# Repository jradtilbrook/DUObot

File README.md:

# DUObot Project Repository

This repository contains the files related to my two-wheeled balancing robot, aptly named DUObot.

In the extremely rare circumstance that someone actually uses this repository and/or finds a bug, please let me know by opening an issue. I would also welcome any other feedback or contributions.

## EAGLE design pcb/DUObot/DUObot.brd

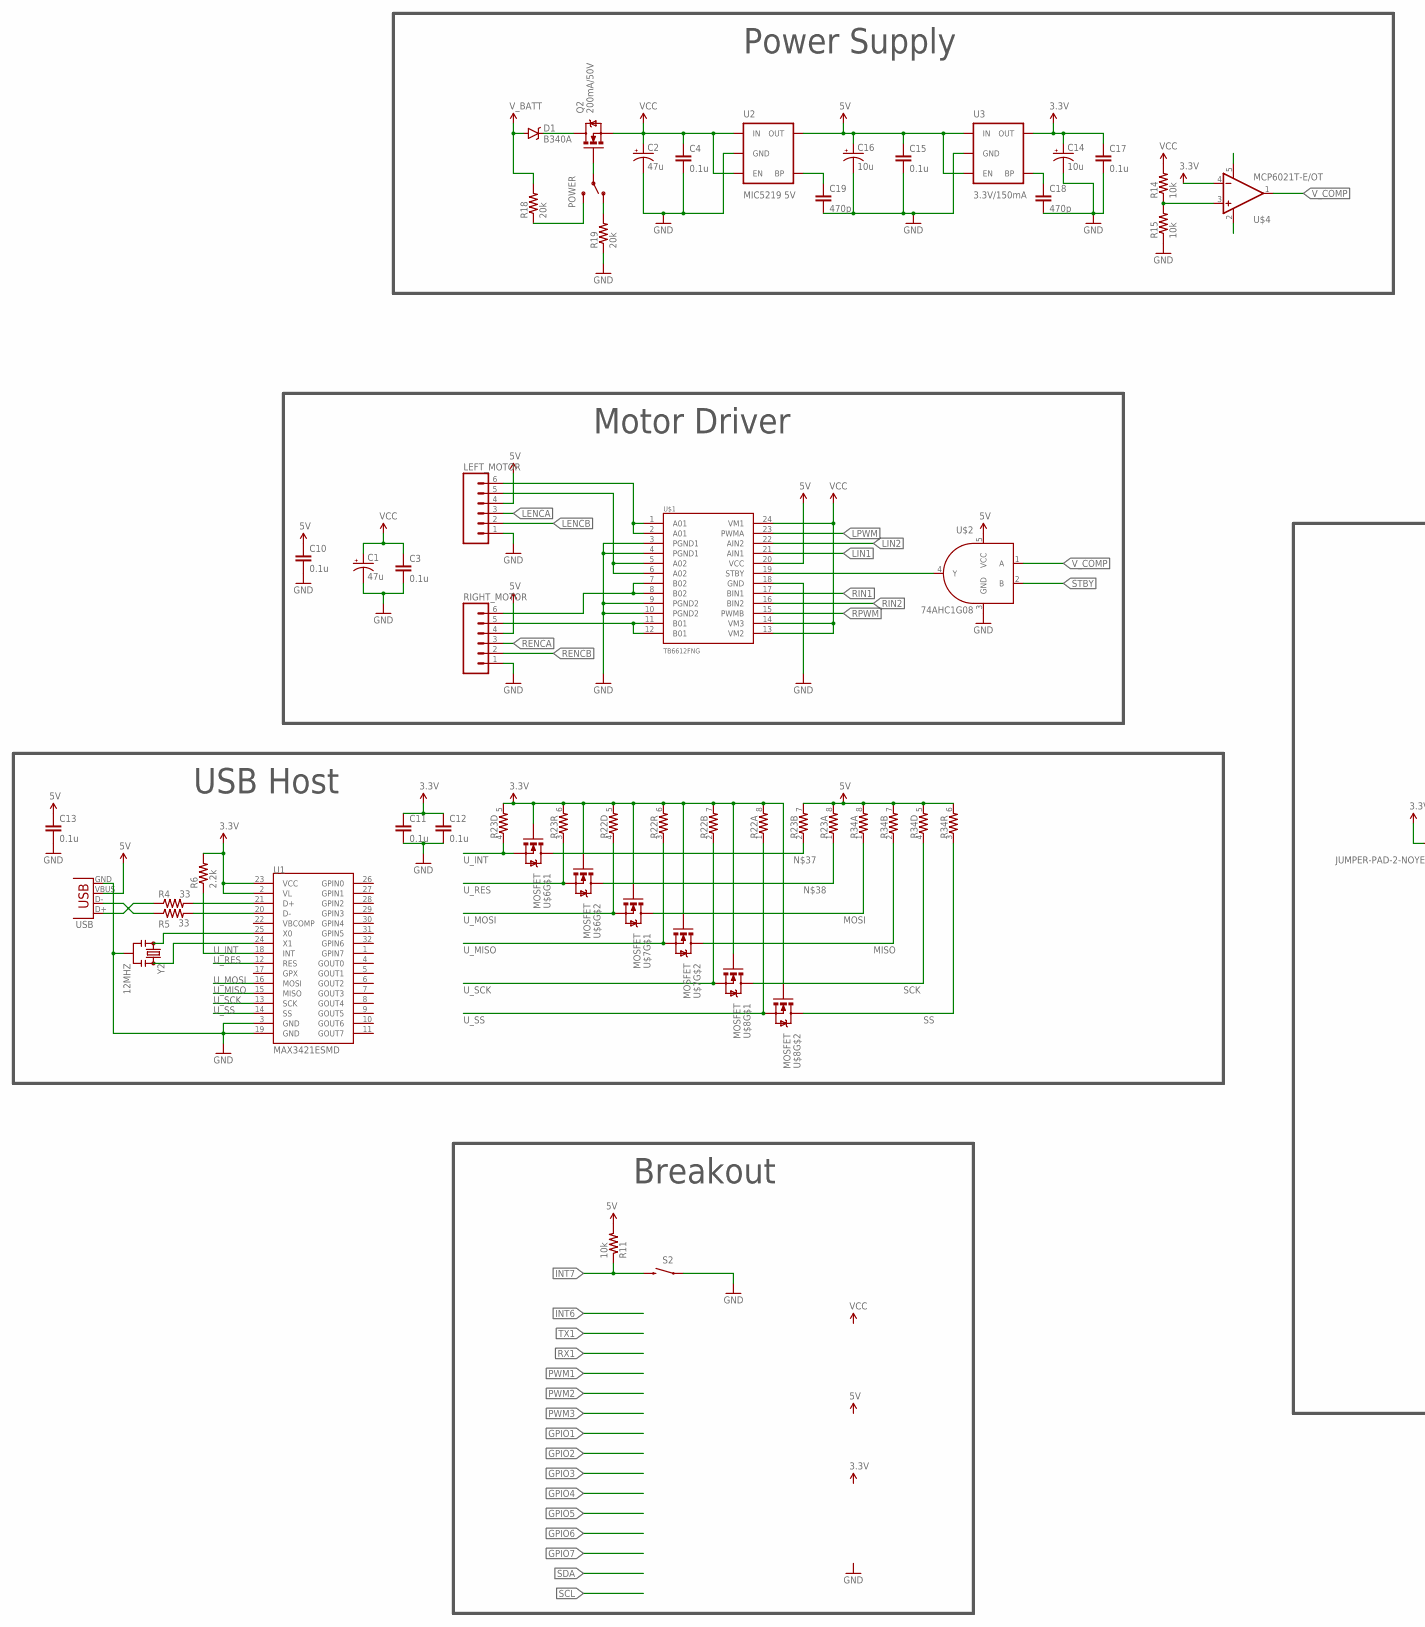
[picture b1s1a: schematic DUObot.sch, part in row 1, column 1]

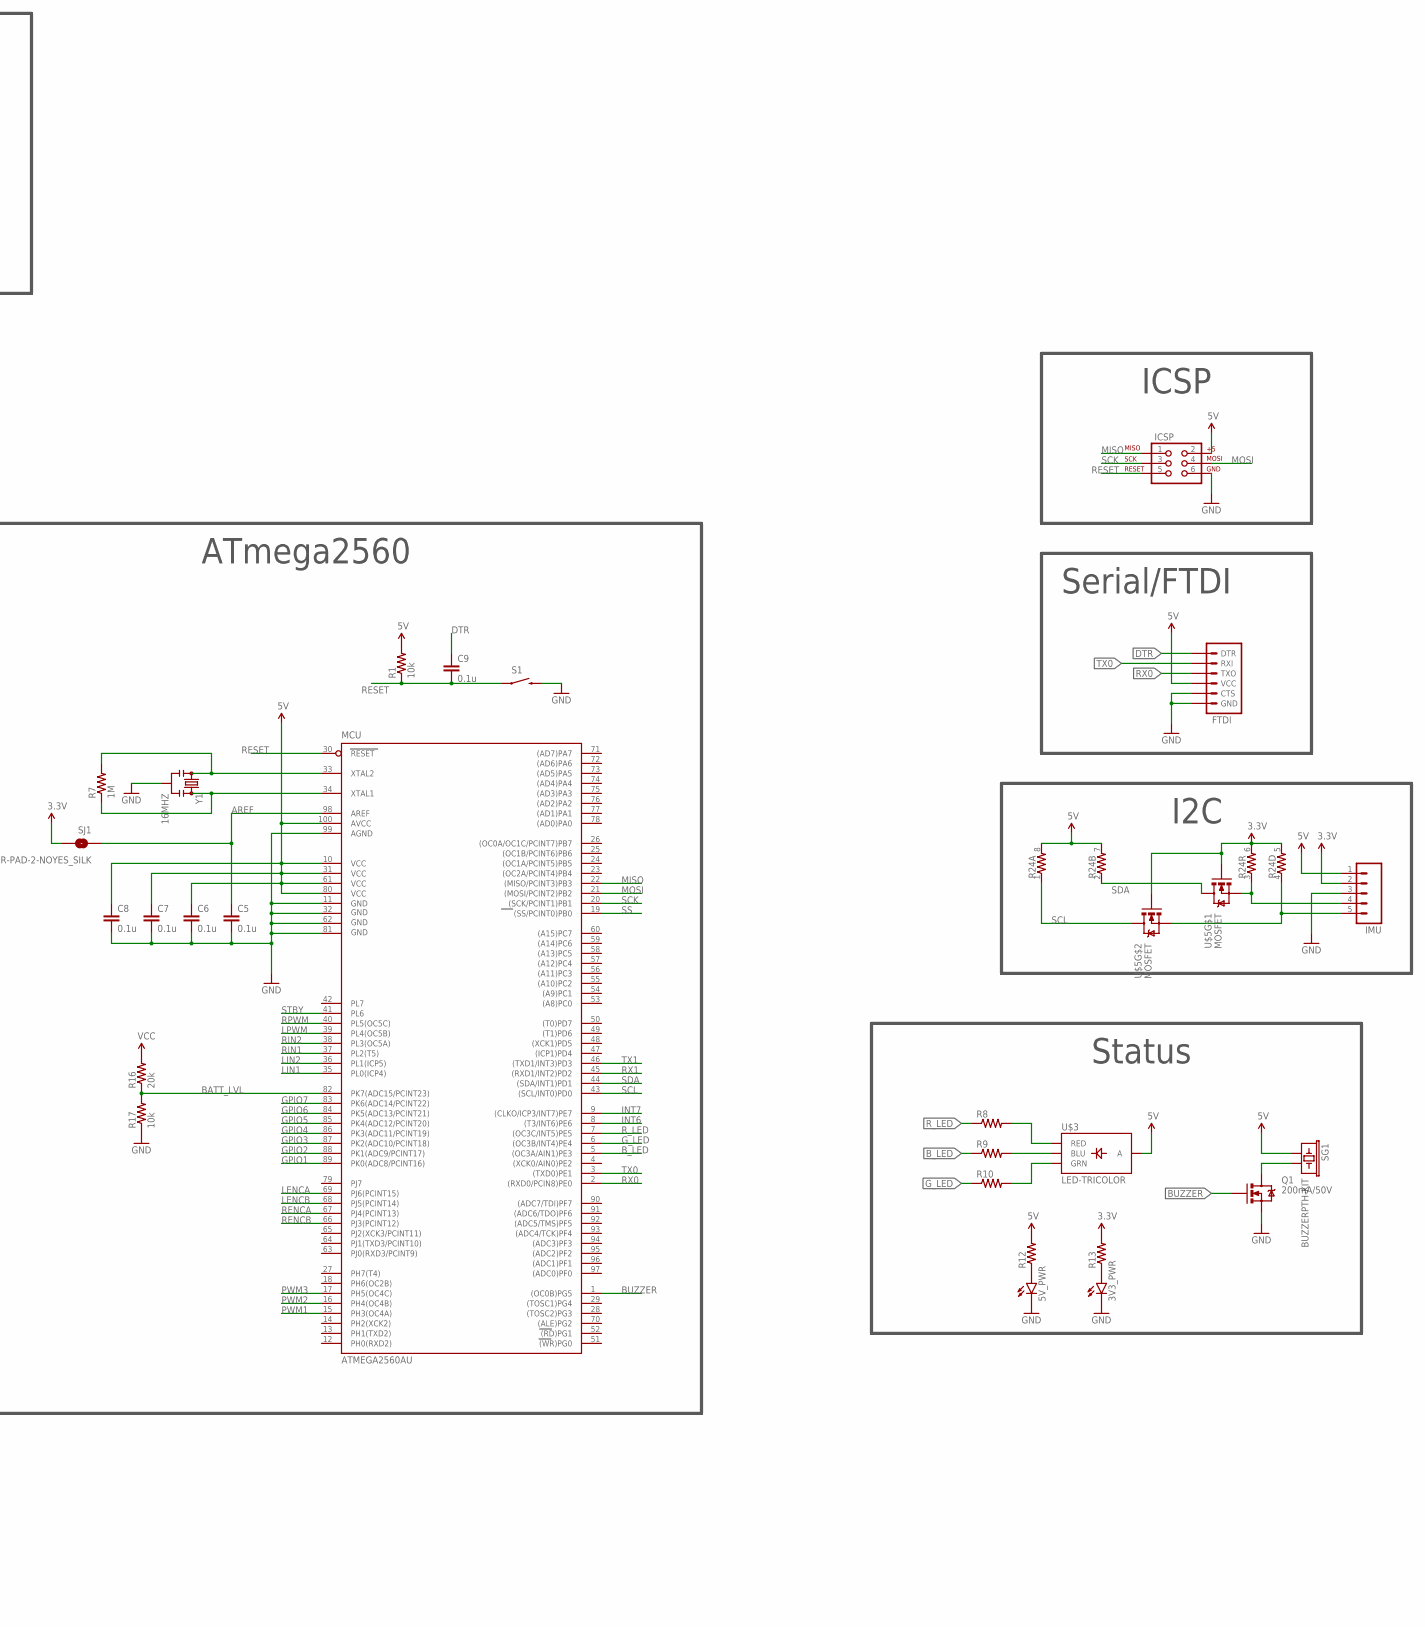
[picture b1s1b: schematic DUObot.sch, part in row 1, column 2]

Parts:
3V3_PWR, 5V_PWR: LED0805; LED-0805
C1, C2: 47u; PANASONIC_D
C3, C4, C5, C6, C7, C8, C9, C10, C11, C12, C13, C15, C17: 0.1u; 0805
C14, C16: 10u; EIA3216
C18, C19: 470p; 0805
D1: B340A; SMA-DIODE
FTDI: ARDUINO_SERIAL_PROGRAMPTH; 1X06
ICSP: AVR_SPI_PRG_6TESTPOINTS; 2X3_TEST_POINTS
IMU: M05SMD2; 1X05-1MM-RA
LEFT_MOTOR: M06SMD-1MM; 1X06-1MM
MCU: ATMEGA2560AU; TQFP100
POWER: SWITCH-SPDT-SMD-A; SWITCH-SPST-SMD-A
Q1, Q2: 200mA/50V; SOT23-3
R1, R11, R14, R15, R17: 10k; 0805
R4, R5: 33; 0805
R6: 2.2k; 0805
R7: 1M; 0805
R8, R9, R10, R12, R13: RESISTOR0805-RES; 0805
R16, R18, R19: 20k; 0805
R22, R23, R24, R34: RESISTOR-ARRAY0603-ARV; 0603-ARV
RIGHT_MOTOR: M06SMD-1MM; 1X06-1MM
S1, S2: SWITCH-MOMENTARY-2SMD-4; TACTILE_SWITCH_TALL
SG1: BUZZERPTH-KIT; BUZZER-12MM-KIT
SJ1: JUMPER-PAD-2-NOYES_SILK; PAD-JUMPER-2-NO_YES_SILK
U1: MAX3421ESMD; TQFP32-5MM
U2: MIC5219 5V; SOT23-5
U3: 3.3V/150mA; SOT23-5
U$1: TB6612FNG; SSOP24
U$2: 74AHC1G08; SOT353
U$3: LED-TRICOLOR; LED-TRICOLOR-SMD
U$4: MCP6021T-E/OT; SOT23-5
U$5, U$6, U$7, U$8: MOSFET; SOT363_V2
USB: USB-A-SMD; USB-A-S-NOSILK-FEMALE
Y1: 16MHZ; RESONATOR-SMD
Y2: 12MHZ; RESONATOR-SMD

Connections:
3.3V: C11.1, C12.1, C14.A (+), C17.1, IMU.2, R6.2, R13.2, R22.5 (2), R22.6 (2), R22.7 (2), R22.8 (2), R23.5 (2), R23.6 (2), R24.5 (2), R24.6 (2), SJ1.2, U1.2 (VL), U1.23 (VCC), U3.5 (OUT), U$4.4 (-IN), U$5.G1 (G), U$5.G2 (G), U$6.G1 (G), U$6.G2 (G), U$7.G1 (G), U$7.G2 (G), U$8.G1 (G), U$8.G2 (G)
5V: C6.1, C7.1, C8.1, C10.1, C13.1, C15.1, C16.A (+), FTDI.4 (VCC), ICSP.2, IMU.1, LEFT_MOTOR.4, MCU.10 (VCC), MCU.31 (VCC1), MCU.61 (VCC2), MCU.80 (VCC3), MCU.100 (AVCC), R1.2, R11.2, R12.2, R23.7 (2), R23.8 (2), R24.7 (2), R24.8 (2), R34.5 (2), R34.6 (2), R34.7 (2), R34.8 (2), RIGHT_MOTOR.4, SG1.+ (1), U2.5 (OUT), U3.1 (IN), U3.3 (EN), U$1.20 (VCC), U$2.5 (VCC), U$3.A, USB.VBUS
AREF: C5.1, MCU.98 (AREF), SJ1.1
BATT_LVL: MCU.82 (PK7(ADC15/PCINT23)), R16.1, R17.2
BUZZER: MCU.1 ((OC0B)PG5), Q1.1 (G)
B_LED: MCU.5 ((OC3A/AIN1)PE3), R9.1
DTR: C9.1, FTDI.1 (DTR)
GND: 3V3_PWR.CATHODE (C), 5V_PWR.CATHODE (C), C1.-, C2.-, C3.2, C4.2, C5.2, C6.2, C7.2, C8.2, C10.2, C11.2, C12.2, C13.2, C14.C (-), C15.2, C16.C (-), C17.2, C18.2, C19.2, FTDI.5 (CTS), FTDI.6 (GND), ICSP.6, IMU.3, LEFT_MOTOR.1, MCU.11 (GND), MCU.32 (GND1), MCU.62 (GND2), MCU.81 (GND3), MCU.99 (AGND), Q1.2 (S), R15.1, R17.1, R19.1, RIGHT_MOTOR.1, S1.B2 (2), S2.A2 (1), U1.3 (GND), U1.19 (GND), U2.2 (GND), U3.2 (GND), U$1.3 (PGND1), U$1.4 (PGND1), U$1.9 (PGND2), U$1.10 (PGND2), U$1.18 (GND), U$2.3 (GND), USB.GND, Y1.2, Y2.2
GPIO1: MCU.89 (PK0(ADC8/PCINT16))
GPIO2: MCU.88 (PK1(ADC9/PCINT17))
GPIO3: MCU.87 (PK2(ADC10/PCINT18))
GPIO4: MCU.86 (PK3(ADC11/PCINT19))
GPIO5: MCU.85 (PK4(ADC12/PCINT20))
GPIO6: MCU.84 (PK5(ADC13/PCINT21))
GPIO7: MCU.83 (PK6(ADC14/PCINT22))
G_LED: MCU.6 ((OC3B/INT4)PE4), R10.1
INT6: MCU.8 ((T3/INT6)PE6)
INT7: MCU.9 ((CLKO/ICP3/INT7)PE7), R11.1, S2.B2 (2)
LENCA: LEFT_MOTOR.3, MCU.69 (PJ6(PCINT15))
LENCB: LEFT_MOTOR.2, MCU.68 (PJ5(PCINT14))
LIN1: MCU.35 (PL0(ICP4)), U$1.21 (AIN1)
LIN2: MCU.36 (PL1(ICP5)), U$1.22 (AIN2)
LPWM: MCU.39 (PL4(OC5B)), U$1.23 (PWMA)
MISO: ICSP.1, MCU.22 ((MISO/PCINT3)PB3), R34.2 (1), U$7.D2 (D)
MOSI: ICSP.4, MCU.21 ((MOSI/PCINT2)PB2), R34.1, U$7.D1 (D)
unnamed: RIGHT_MOTOR.5, U$1.11 (B01), U$1.12 (B01)
unnamed: RIGHT_MOTOR.6, U$1.7 (B02), U$1.8 (B02)
unnamed: LEFT_MOTOR.6, U$1.1 (A01), U$1.2 (A01)
unnamed: LEFT_MOTOR.5, U$1.5 (A02), U$1.6 (A02)
unnamed: MCU.33 (XTAL2), R7.2, Y1.1
unnamed: MCU.34 (XTAL1), R7.1, Y1.3
unnamed: R4.1, USB.D+
unnamed: R5.2, U1.20 (D-)
unnamed: R4.2, U1.21 (D+)
unnamed: R5.1, USB.D-
unnamed: R14.1, R15.2, U$4.3 (+IN)
unnamed: U$1.19 (STBY), U$2.4 (Y)
unnamed: Q1.3 (D), SG1.- (2)
unnamed: R9.2, U$3.B (BLU)
unnamed: R8.2, U$3.R (RED)
unnamed: R10.2, U$3.G (GRN)
unnamed: 5V_PWR.ANODE (A), R12.1
unnamed: 3V3_PWR.ANODE (A), R13.1
unnamed: U1.25 (X0), Y2.1
unnamed: U1.24 (X1), Y2.3
unnamed: C19.1, U2.4 (BP)
unnamed: C18.1, U3.4 (BP)
unnamed: D1.C, Q2.3 (D)
unnamed: POWER.1 (O), R19.2
unnamed: POWER.3 (S), R18.1
unnamed: POWER.2, Q2.1 (G)
unnamed: IMU.4, R24.3 (1), U$5.S1 (S)
unnamed: IMU.5, R24.4 (1), U$5.S2 (S)
unnamed: R23.2 (1), U$6.D1 (D)
unnamed: R23.1, U$6.D2 (D)
PWM1: MCU.15 (PH3(OC4A))
PWM2: MCU.16 (PH4(OC4B))
PWM3: MCU.17 (PH5(OC4C))
RENCA: MCU.67 (PJ4(PCINT13)), RIGHT_MOTOR.3
RENCB: MCU.66 (PJ3(PCINT12)), RIGHT_MOTOR.2
RESET: C9.2, ICSP.5, MCU.30 (RESET), R1.1, S1.A2 (1)
RIN1: MCU.37 (PL2(T5)), U$1.17 (BIN1)
RIN2: MCU.38 (PL3(OC5A)), U$1.16 (BIN2)
RPWM: MCU.40 (PL5(OC5C)), U$1.15 (PWMB)
RX0: FTDI.3 (TXO), MCU.2 ((RXD0/PCIN8)PE0)
RX1: MCU.45 ((RXD1/INT2)PD2)
R_LED: MCU.7 ((OC3C/INT5)PE5), R8.1
SCK: ICSP.3, MCU.20 ((SCK/PCINT1)PB1), R34.4 (1), U$8.D1 (D)
SCL: MCU.43 ((SCL/INT0)PD0), R24.1, U$5.D2 (D)
SDA: MCU.44 ((SDA/INT1)PD1), R24.2 (1), U$5.D1 (D)
SS: MCU.19 ((SS/PCINT0)PB0), R34.3 (1), U$8.D2 (D)
STBY: MCU.41 (PL6), U$2.2 (B)
TX0: FTDI.2 (RXI), MCU.3 ((TXD0)PE1)
TX1: MCU.46 ((TXD1/INT3)PD3)
U_INT: R6.1, R23.4 (1), U1.18 (INT), U$6.S1 (S)
U_MISO: R22.3 (1), U1.15 (MISO), U$7.S2 (S)
U_MOSI: R22.4 (1), U1.16 (MOSI), U$7.S1 (S)
U_RES: R23.3 (1), U1.12 (RES), U$6.S2 (S)
U_SCK: R22.2 (1), U1.13 (SCK), U$8.S1 (S)
U_SS: R22.1, U1.14 (SS), U$8.S2 (S)
VCC: C1.+, C2.+, C3.1, C4.1, Q2.2 (S), R14.2, R16.2, U2.1 (IN), U2.3 (EN), U$1.13 (VM2), U$1.14 (VM3), U$1.24 (VM1)
V_BATT: D1.A, R18.2
V_COMP: U$2.1 (A), U$4.1 (OUT)

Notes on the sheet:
ICSP
Serial/FTDI
I2C
Motor Driver
USB Host
ATmega2560
Power Supply
Status
Breakout

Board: 2 copper layers, 70 parts (1 on the bottom side), 70 nets, no tracks yet.

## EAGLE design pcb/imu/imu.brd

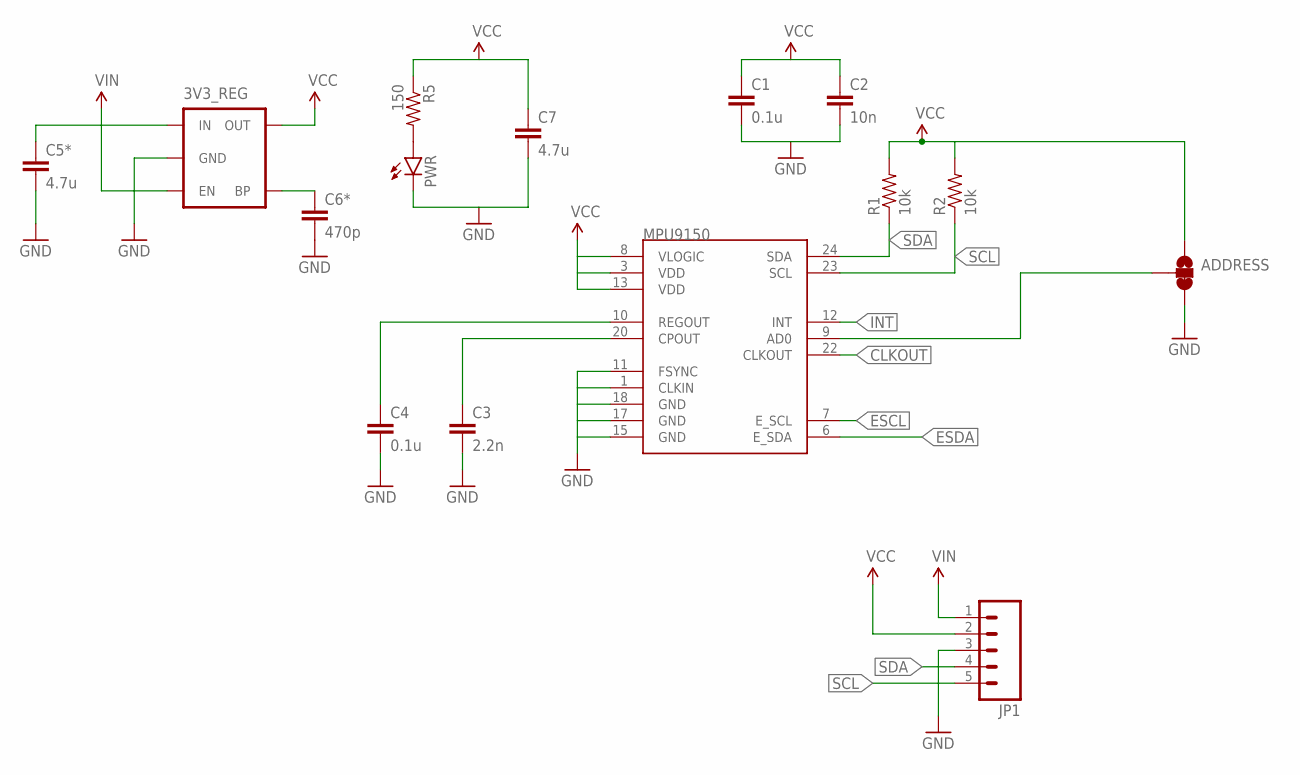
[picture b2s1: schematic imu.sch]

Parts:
3V3_REG: MIC52053.3V; SOT23-5
ADDRESS: JUMPER-PAD-3-2OF3_NC_BY_TRACE_SMALL; PAD-JUMPER-3-2OF3_NC_BY_TRACE_YES_SILK_FULL_BOX
C1, C4: 0.1u; 0805
C2: 10n; 0805
C3: 2.2n; 0805
C5*, C7: 4.7u; 0805
C6*: 470p; 0805
JP1: M05SMD2; 1X05-1MM-RA
MPU9150: MPU-9150QFN-24-NP; QFN-24-NP
PWR: LED0805; LED-0805
R1, R2: 10k; 0805
R5: 150; 0805

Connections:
AD0: ADDRESS.2, MPU9150.9 (AD0)
CLKOUT: MPU9150.22 (CLKOUT)
ESCL: MPU9150.7 (E_SCL)
ESDA: MPU9150.6 (E_SDA)
GND: 3V3_REG.2 (GND), ADDRESS.3, C1.2, C2.2, C3.2, C4.2, C5*.2, C6*.2, C7.2, JP1.3, MPU9150.1 (CLKIN), MPU9150.11 (FSYNC), MPU9150.15 (GND), MPU9150.17 (GND), MPU9150.18 (GND), PWR.CATHODE (C)
INT: MPU9150.12 (INT)
unnamed: PWR.ANODE (A), R5.2
unnamed: C3.1, MPU9150.20 (CPOUT)
unnamed: C4.1, MPU9150.10 (REGOUT)
unnamed: 3V3_REG.4 (BP), C6*.1
SCL: JP1.5, MPU9150.23 (SCL), R2.1
SDA: JP1.4, MPU9150.24 (SDA), R1.1
VCC: 3V3_REG.5 (OUT), ADDRESS.1, C1.1, C2.1, C7.1, JP1.2, MPU9150.3 (VDD), MPU9150.8 (VLOGIC), MPU9150.13 (VDD), R1.2, R2.2, R5.1
VIN: 3V3_REG.1 (IN), 3V3_REG.3 (EN), C5*.1, JP1.1

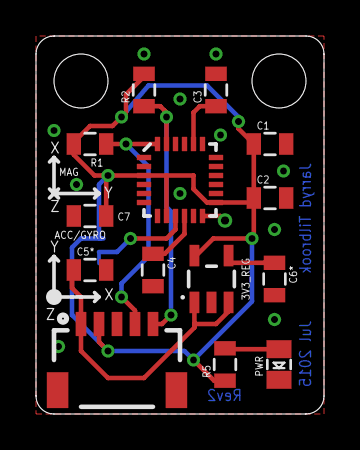
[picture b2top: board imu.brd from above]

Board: 2 copper layers, 16.0 x 21.0 mm, 15 parts (1 on the bottom side), 10 nets.

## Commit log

2015-07-08 Initial commit. Add README and gitignore
2015-07-08 Add pcb design projects. Update README
2015-07-08 Add blank Arduino sketch
2015-07-09 Add components to MPU breakout. Needs board layout and revision
2015-07-09 Change LED to 0805 package
2015-07-10 Finish MPU board layout revision 1
2015-07-10 MPU revision 2 with 3mm holes
2015-07-10 Add IMU axes to silkscreen
2015-07-10 Finalise IMU board schematic/layout. Try to make 3D model (*.emn/emp) files
2015-07-10 Update readme to reflect todo list
2015-07-10 Modify readme list
2015-07-13 Revise IMU board - add date and board title
2015-07-13 Finalise rev2 board, add IMU parts list
2015-07-14 Add datasheets for some components
2015-07-14 Add more components to main board. Start pcb layout
2015-07-16 Add more datasheets and explanation to readme
2015-07-16 Continue adding components to schematic
2015-07-16 Working on power select control circuitry
2015-07-17 Finalise parts list for IMU breakout
2015-07-17 Main board mostly finished - needs minor changes/additions
2015-07-17 Change individual pull-up resistors to arrays
2015-07-27 TODO: Upgrade imu to MPU-9250 for future revisions
2016-01-30 Add CAD models and MPU6050 datasheets
2016-07-11 Remove old files ready for mkV
2016-07-11 Add skeleton for motor module
2016-07-12 Implement Motor class methods
2016-09-13 Add quadrature decoder class
2016-09-13 Clean line length
2016-09-14 Add license

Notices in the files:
parts and their libraries:
SparkFun-Connectors: Licensing: Creative Commons ShareAlike 4.0 International - https://creativecommons.org/licenses/by-sa/4.0
